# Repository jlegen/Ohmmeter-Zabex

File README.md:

# Ohmmeter (Zabex)
realtime ohm meter - shows value and the related E24 value in half a second (or less)

Maybe you always have a lot of loose resistors lying around after your breadboard experiments, 
because sorting them back into the compartments is annoying and awkward.
Then this thing is for you...

* original project: http://www.zabex.de/site/ohmmeter.html
* modified for using LiIon cell: https://www.mikrocontroller.net/topic/489461
* this version here is just a PCB to make it easy to build this little helper gadget; it uses a standard 0802 LCD display, which is easily available
* the footprint of the MCP1640 seems a bit odd - pin 1 is at the lower right (see photo)

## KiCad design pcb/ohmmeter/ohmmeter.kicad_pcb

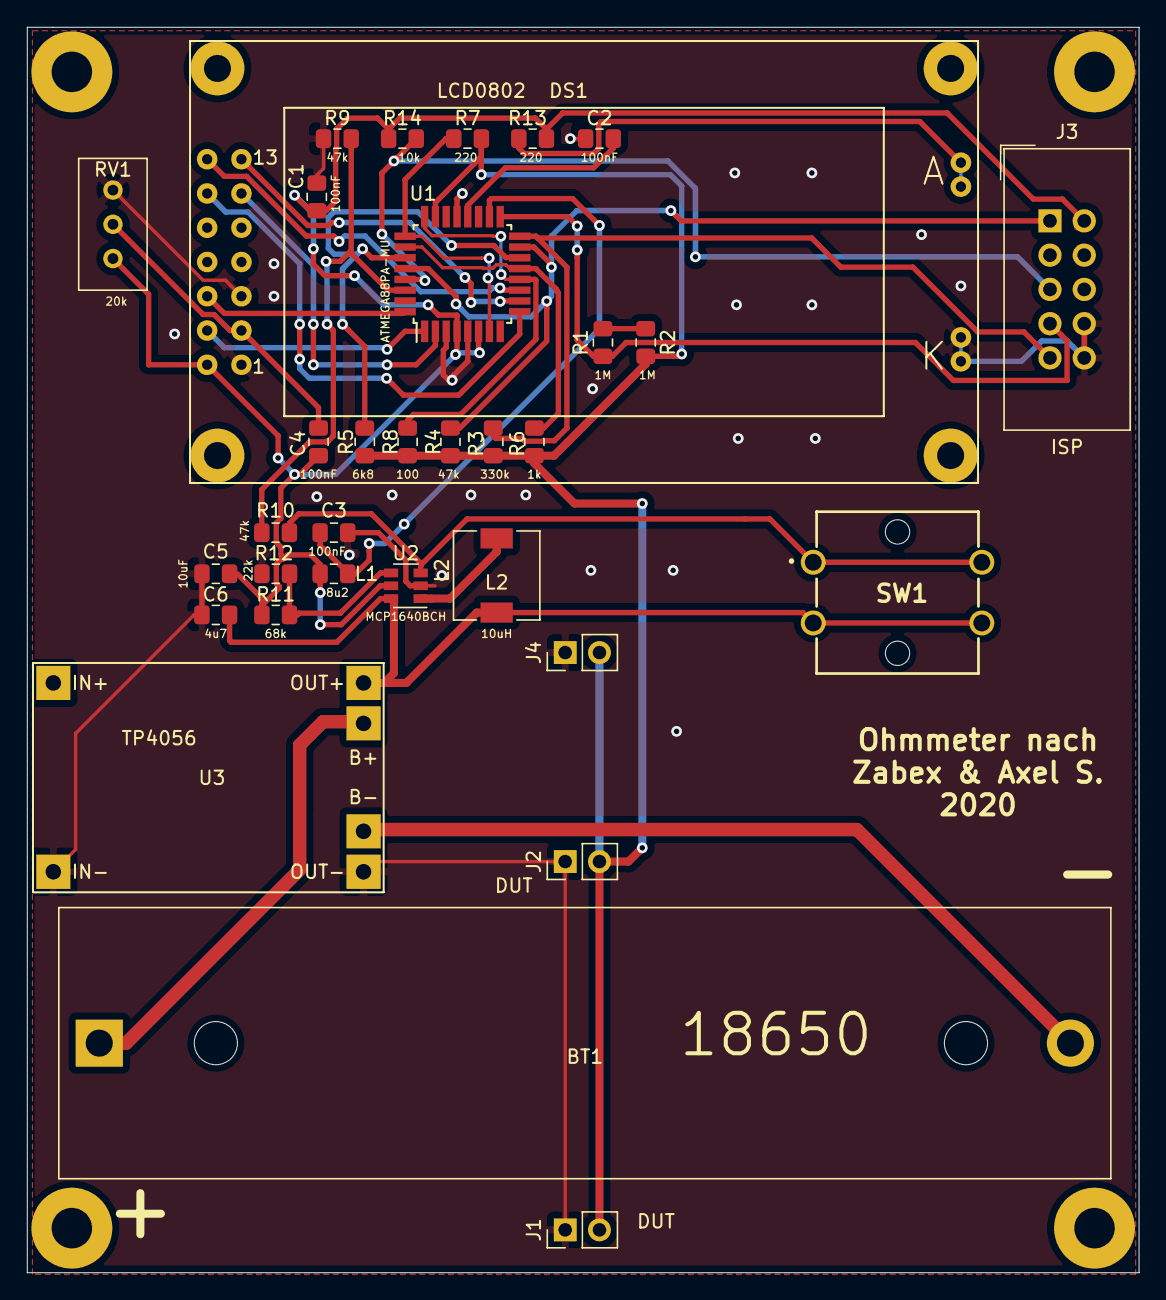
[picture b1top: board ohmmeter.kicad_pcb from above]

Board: 2 copper layers, 82.4 x 92.3 mm, 37 parts (0 on the bottom side), 29 nets.

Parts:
BT1: 18650; BatteryHolder_MPD_BH-18650-PC2
C1, C2, C3, C4: 100nF; C_0805_2012Metric_Pad1.15x1.40mm_HandSolder
C5: 10uF; C_0805_2012Metric_Pad1.15x1.40mm_HandSolder
C6: 4u7; C_0805_2012Metric_Pad1.15x1.40mm_HandSolder
DS1: LCD0802
H1, H2, H3, H4: MountingHole; MountingHole_3mm_Pad
J1, J2, J4: DUT; PinHeader_1x02_P2.54mm_Vertical
J3: ISP; IDC-Header_2x05_P2.54mm_Vertical
L1: 8u2; L_0805_2012Metric_Pad1.15x1.40mm_HandSolder
L2: 10uH; L_6.3x6.3_H3
R1, R2: 1M; R_0805_2012Metric_Pad1.15x1.40mm_HandSolder
R3: 330k; R_0805_2012Metric_Pad1.15x1.40mm_HandSolder
R4, R9, R10: 47k; R_0805_2012Metric_Pad1.15x1.40mm_HandSolder
R5: 6k8; R_0805_2012Metric_Pad1.15x1.40mm_HandSolder
R6: 1k; R_0805_2012Metric_Pad1.15x1.40mm_HandSolder
R7, R13: 220; R_0805_2012Metric_Pad1.15x1.40mm_HandSolder
R8: 100; R_0805_2012Metric_Pad1.15x1.40mm_HandSolder
R11: 68k; R_0805_2012Metric_Pad1.15x1.40mm_HandSolder
R12: 22k; R_0805_2012Metric_Pad1.15x1.40mm_HandSolder
R14: 10k; R_0805_2012Metric_Pad1.15x1.40mm_HandSolder
RV1: 20k; Potentiometer_Bourns_3296W_Vertical
SW1: SW_Push; B3F-4000
U1: ATMEGA88PA-MU; TQFP-32_7x7mm_P0.8mm
U2: MCP1640BCH; SOT-23-6
U3: TP4056

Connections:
+5V: C1.1, C4.2, C5.1, DS1.2, J3.2, L1.1, R11.1, R13.1, R14.1, RV1.1, U1.4, U1.6, U2.5
AVCC: C3.1, L1.2, U1.18
GND: C1.2, C2.2, C3.2, C5.2, C6.2, DS1.1, DS1.5, DS1.16, J1.1, J2.1, J3.8, J3.10, J4.1, R9.1, R12.1, RV1.3, U1.3, U1.5, U1.21, U2.2, U3.2, U3.3
unnamed: BT1.1, U3.5
unnamed: BT1.2, U3.4
unnamed: C2.1, U1.20
unnamed: C4.1, DS1.3, RV1.2
unnamed: C6.1, L2.1, SW1.3, SW1.4, U2.6, U3.6
unnamed: DS1.4, U1.1
unnamed: DS1.6, U1.32
unnamed: DS1.11, U1.2
unnamed: DS1.12, U1.9
unnamed: DS1.13, U1.10
unnamed: DS1.14, U1.11
unnamed: DS1.15, R13.2
unnamed: J1.2, J2.2, J4.2, R2.2, R3.2, R4.2, R5.2, R6.2, R7.2, R8.2, U1.23
unnamed: J3.1, R4.1, U1.15, U1.28
unnamed: J3.5, R14.2, U1.29
unnamed: J3.7, R1.1, U1.17
unnamed: J3.9, R3.1, U1.16
unnamed: L2.2, U2.1
unnamed: R1.2, R2.1
unnamed: R5.1, U1.14, U1.27
unnamed: R6.1, U1.13, U1.26
unnamed: R7.1, U1.7, U1.25
unnamed: R8.1, U1.12, U1.24
unnamed: R10.1, SW1.1, SW1.2, U2.3
unnamed: R9.2, R10.2, U1.30
unnamed: R11.2, R12.2, U2.4

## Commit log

2020-10-06 Update README.md
    initial start
2020-10-06 initial upload
    upload of pcb and sources
2020-10-06 PCB re-upload
    Kicad 5.1.7 fix
2020-10-06 PCB update
    fixed silk
